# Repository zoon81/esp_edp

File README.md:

# ESP8266 ePaperDisplay<br>
## This project will bring life into ePaper displays and IoT applications.<br>
### This project is made under the term of my university research.
I'm going to use the 1.54 inch ePaper display from waveshare and it is driven by an ESP8266 based NodeMCU v3.<br>
I'm using the NonOS SDK from Espressif.<br>

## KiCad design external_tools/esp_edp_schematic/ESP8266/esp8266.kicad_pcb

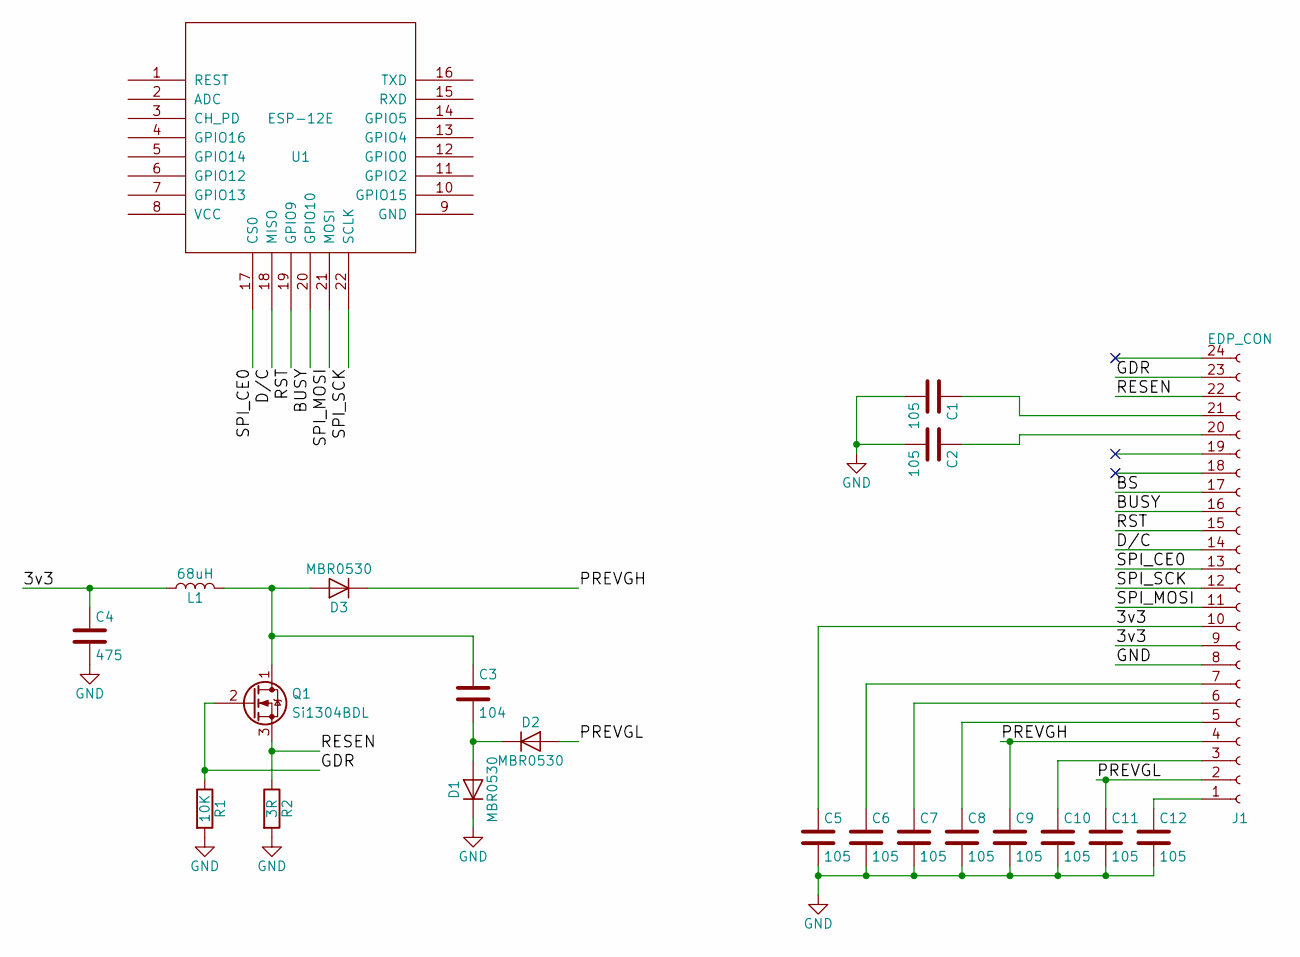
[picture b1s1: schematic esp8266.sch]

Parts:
C1, C2, C5, C6, C7, C8, C9, C10, C11, C12: 105; C_0805_HandSoldering
C3: 104; C_0805_HandSoldering
C4: 475; C_0805_HandSoldering
D1, D2, D3: MBR0530; D_SOD-123
J1: EDP_CON; FPC-24pin-0.5mm
L1: 68uH; L_1206_HandSoldering
Q1: Si1304BDL; SOT-23
R1: 10K; R_0805_HandSoldering
R2: 3R; R_0805_HandSoldering
U1: ESP-12E

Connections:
/3v3: C4.1, C5.1, J1.9, J1.10, L1.1
/BS: J1.17
/BUSY: J1.16, U1.20 (GPIO10)
/D/C: J1.14, U1.18 (MISO)
/GDR: J1.23, Q1.2 (G), R1.1
/PREVGH: C9.1, D3.1 (K), J1.4
/PREVGL: C11.1, D2.2 (A), J1.2
/RESEN: J1.22, Q1.3 (S), R2.1
/RST: J1.15, U1.19 (GPIO9)
/SPI_CE0: J1.13, U1.17 (CS0)
/SPI_MOSI: J1.11, U1.21 (MOSI)
/SPI_SCK: J1.12, U1.22 (SCLK)
GND: C1.2, C2.2, C4.2, C5.2, C6.2, C7.2, C8.2, C9.2, C10.2, C11.2, C12.2, D1.1 (K), J1.8, R1.2, R2.2
unnamed: C1.1, J1.21
unnamed: C2.1, J1.20
unnamed: C3.1, D3.2 (A), L1.2, Q1.1 (D)
unnamed: C3.2, D1.2 (A), D2.1 (K)
unnamed: C6.1, J1.7
unnamed: C7.1, J1.6
unnamed: C8.1, J1.5
unnamed: C10.1, J1.3
unnamed: C12.1, J1.1

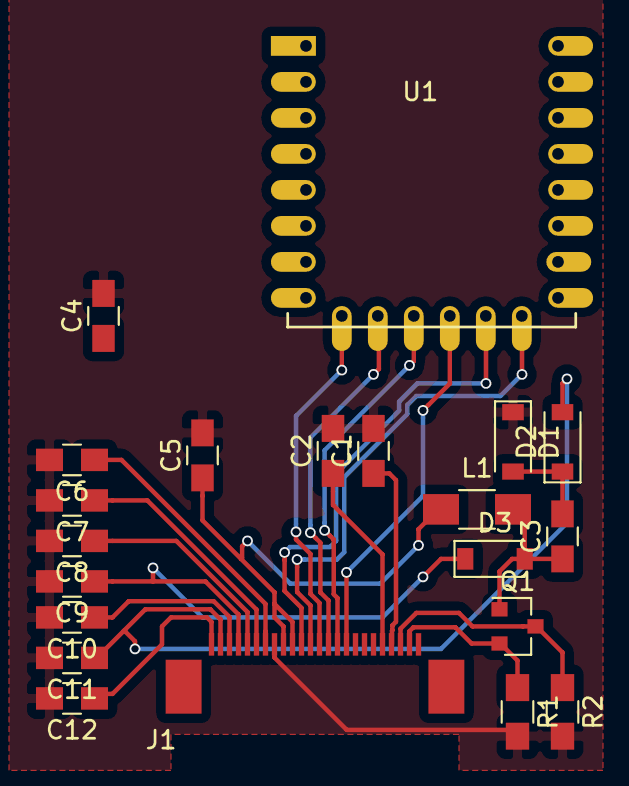
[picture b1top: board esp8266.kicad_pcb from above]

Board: 2 copper layers, 21 parts (0 on the bottom side), 21 nets.

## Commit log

2017-11-10 First
2017-11-12 EDP driver implementation in progress.
2017-11-13 more update
2017-11-14 Working Epd Driver.
2017-11-16 Font strucuring and UI handling improvments
2017-11-16 Icon subsystem basics added
2017-11-18 Icons data stored in FLASH instead of RAM
2017-11-19 Basic weather icons in FLASH space working now. EDP driver polishing. Python utility for converting 8bit image data array to 32bit (alpha stage).
2017-11-20 font for weather temperature in FLASH
2017-11-23 Icons subsytem refactoring
2017-11-24 Icon bitmap generator update
2017-11-24 Json parsing & widget subsytem improvments
2017-11-24 exclude files from tracking
2017-11-24 Custom linker script
2017-11-28 WeatherWidget developmnet:<br> Get current weather working<br> Openweathermap not applicable for forcast<br> Darktsky forecast API initialization
2017-11-28 Succesfully stached my icon generator "-_-, updated icon bitmaps, added icon resources
2017-11-29 This commit not runnig currectly, (missing icons). Status update only!
2017-11-30 mac support for makefile
2017-11-30 font map update
2017-11-30 Current weather allmost done
2017-11-30 Local date/time by timezonedb.net This data needed for the weather forcast, darksky.net timemashine API.
2017-12-01 DarkSky.net and forecast are partialy working.
2017-12-02 Early final version. Polishing welcommed in the future. Json parsing bug still exist.
2017-12-02 Remove some files
2017-12-03 Proof of Concept schematic added
2018-02-13 spiffs
2018-02-20 Basic file system structure plans
2018-02-21 flash_write and filesystem practicing
2018-02-22 FileSystem progress
2018-02-25 FS : index page reading
2018-03-05 Filesystem meta page parsing
2018-03-06 File system development
2018-03-20 file level acces,can read files from file system based on fileheader
2018-03-29 Filesystem, writing to it is in progress
2018-03-30 small FS update
2018-03-31 FS update
2018-05-08 Almost done, FS update
